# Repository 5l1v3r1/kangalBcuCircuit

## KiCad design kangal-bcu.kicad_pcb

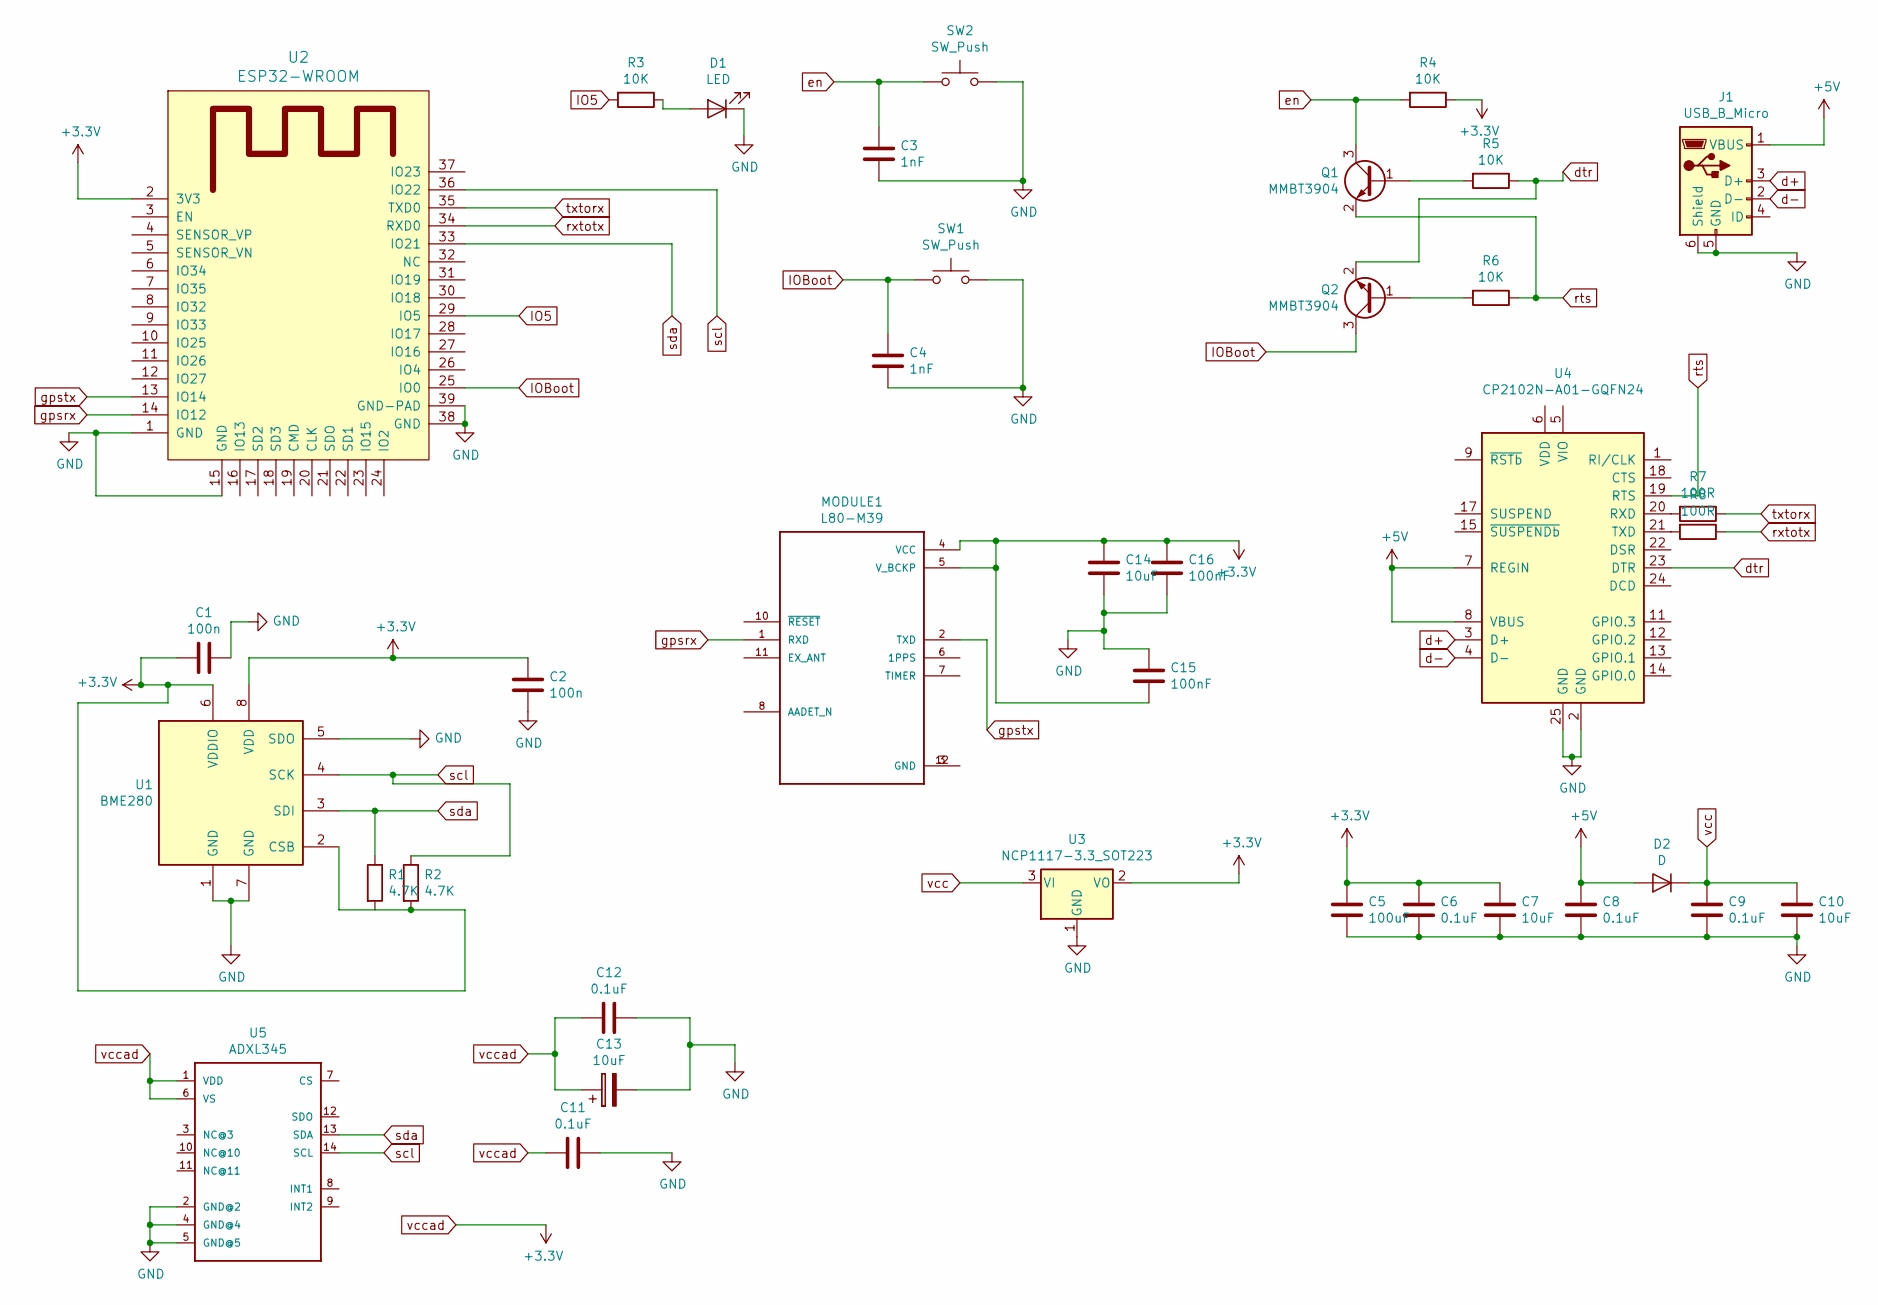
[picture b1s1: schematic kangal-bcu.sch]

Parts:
C1, C2: 100n; C_0805_2012Metric
C3, C4: 1nF; C_0805_2012Metric
C5: 100uF; C_0805_2012Metric
C6, C8, C9, C11, C12: 0.1uF; C_0805_2012Metric
C7, C10, C13, C14: 10uF; C_0805_2012Metric
C15, C16: 100nF; C_0805_2012Metric
D1: LED; LED_0805_2012Metric
D2: D; D_0805_2012Metric
J1: USB_B_Micro; USB_Micro-B_Amphenol_10103594-0001LF_Horizontal
MODULE1: L80-M39; QUECTEL_L80-M39
Q1, Q2: MMBT3904; SOT-23
R1, R2: 4.7K; R_0805_2012Metric
R3, R4, R5, R6: 10K; R_0805_2012Metric
R7, R8: 100R; R_0805_2012Metric
SW1, SW2: SW_Push; SW_SPST_PTS645
U1: BME280; Bosch_LGA-8_2.5x2.5mm_P0.65mm_ClockwisePinNumbering
U2: ESP32-WROOM; ESP32-WROOM-32
U3: NCP1117-3.3_SOT223; SOT-223-3_TabPin2
U4: CP2102N-A01-GQFN24; QFN-24-1EP_4x4mm_P0.5mm_EP2.6x2.6mm
U5: ADXL345; LGA-14

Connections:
+5V: C8.1, D2.2 (A), J1.1 (VBUS), U4.7 (REGIN), U4.8 (VBUS)
GND: C1.2, C2.2, C3.2, C4.2, C5.2, C6.2, C7.2, C8.2, C9.2, C10.2, C11.2, C12.1, C13.2, C14.1, C15.1, C16.2, D1.1 (K), J1.5 (GND), J1.6 (Shield), SW1.2, SW2.2, U1.1 (GND), U1.5 (SDO), U1.7 (GND), U2.1 (GND), U2.15 (GND), U2.38 (GND), U2.39 (GND-PAD), U3.1 (GND), U4.2 (GND), U4.25 (GND), U5.2 (GND@2), U5.4 (GND@4), U5.5 (GND@5)
IO5: R3.2, U2.29 (IO5)
IOBoot: C4.1, Q2.3 (C), SW1.1, U2.25 (IO0)
unnamed: D1.2 (A), R3.1
unnamed: MODULE1.3 (GND), MODULE1.12 (GND)
unnamed: Q1.1 (B), R5.2
unnamed: Q2.1 (B), R6.2
unnamed: R7.2, U4.20 (RXD)
unnamed: R8.2, U4.21 (TXD)
d+: J1.3 (D+), U4.3 (D+)
d-: J1.2 (D-), U4.4 (D-)
dtr: Q2.2 (E), R5.1, U4.23 (DTR)
en: C3.1, Q1.3 (C), R4.2, SW2.1
gpsrx: MODULE1.1 (RXD), U2.14 (IO12)
gpstx: MODULE1.2 (TXD), U2.13 (IO14)
rts: Q1.2 (E), R6.1, U4.19 (RTS)
rxtotx: R8.1, U2.34 (RXD0)
scl: R2.1, U1.4 (SCK), U2.36 (IO22), U5.14 (SCL)
sda: R1.1, U1.3 (SDI), U2.33 (IO21), U5.13 (SDA)
txtorx: R7.1, U2.35 (TXD0)
vcc: C9.1, C10.1, D2.1 (K), U3.3 (VI)
vccad: C1.1, C2.1, C5.1, C6.1, C7.1, C11.1, C12.2, C13.1, C14.2, C15.2, C16.1, MODULE1.4 (VCC), MODULE1.5 (V_BCKP), R1.2, R2.2, R4.1, U1.2 (CSB), U1.6 (VDDIO), U1.8 (VDD), U2.2 (3V3), U3.2 (VO), U5.1 (VDD), U5.6 (VS)

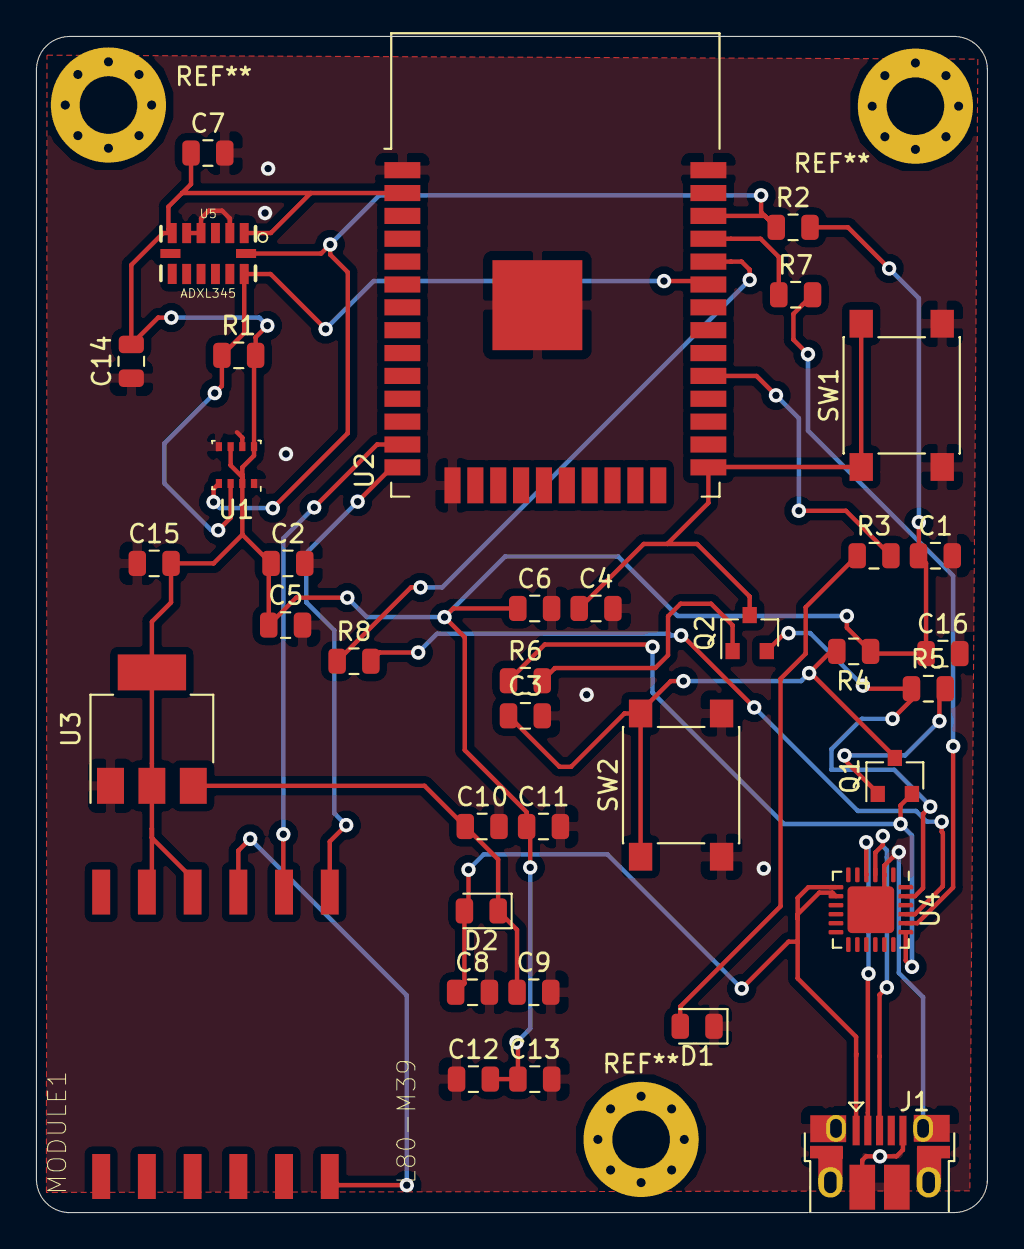
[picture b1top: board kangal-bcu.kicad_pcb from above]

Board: 2 copper layers, 52.8 x 65.3 mm, 37 parts (0 on the bottom side), 23 nets.
